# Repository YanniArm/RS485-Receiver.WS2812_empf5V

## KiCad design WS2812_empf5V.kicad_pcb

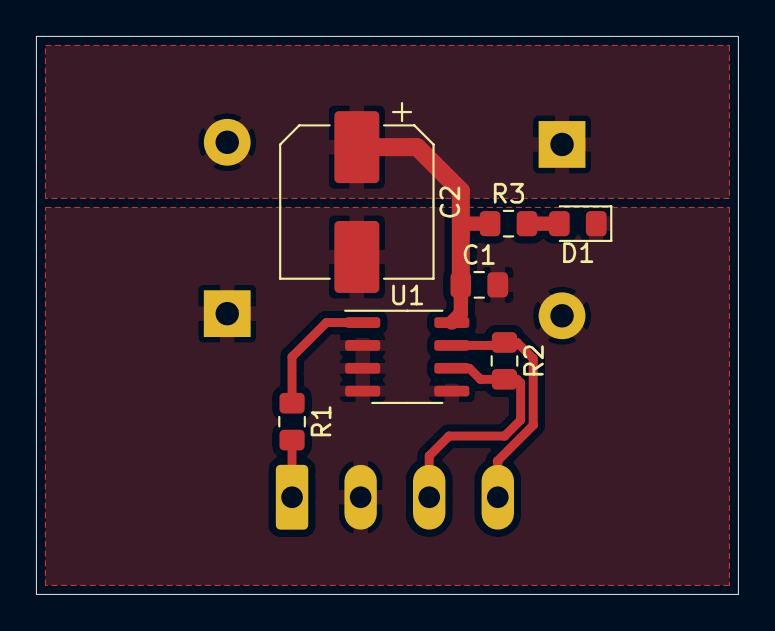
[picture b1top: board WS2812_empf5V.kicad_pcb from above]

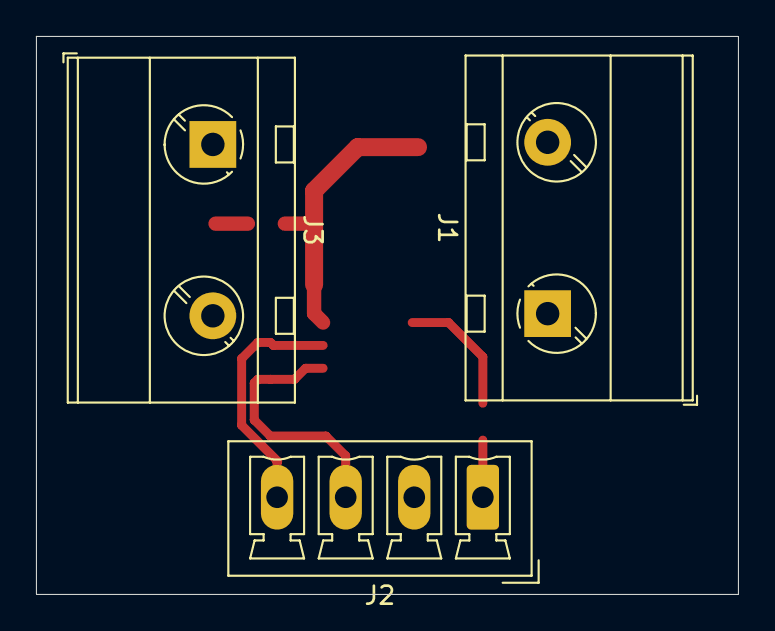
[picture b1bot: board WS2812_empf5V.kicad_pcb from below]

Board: 2 copper layers, 39.0 x 31.0 mm, 10 parts (3 on the bottom side), 7 nets.

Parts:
C1: C; C_0805_2012Metric_Pad1.15x1.40mm_HandSolder
C2: CP; CP_Elec_8x6.5
D1: LED; LED_0805_2012Metric_Pad1.15x1.40mm_HandSolder
J1, J3: Conn_01x02_Female; TerminalBlock_MetzConnect_Type703_RT10N02HGLU_1x02_P9.52mm_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
J2: Conn_01x04_Male; PhoenixContact_MCV_1,5_4-G-3.81_1x04_P3.81mm_Vertical
R1, R3: R; R_0805_2012Metric_Pad1.15x1.40mm_HandSolder
R2: 120; R_0805_2012Metric_Pad1.15x1.40mm_HandSolder
U1: MAX485E; SOIC-8_3.9x4.9mm_P1.27mm

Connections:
+5V: C1.1, C2.1, J1.2, J3.1, R3.1, U1.8
GND: C1.2, C2.2, D1.1, J1.1, J2.2, J3.2, U1.2, U1.3, U1.4, U1.5
unnamed: D1.2, R3.2
unnamed: J2.1, R1.2
unnamed: J2.3, R2.2, U1.6
unnamed: J2.4, R2.1, U1.7
unnamed: R1.1, U1.1
